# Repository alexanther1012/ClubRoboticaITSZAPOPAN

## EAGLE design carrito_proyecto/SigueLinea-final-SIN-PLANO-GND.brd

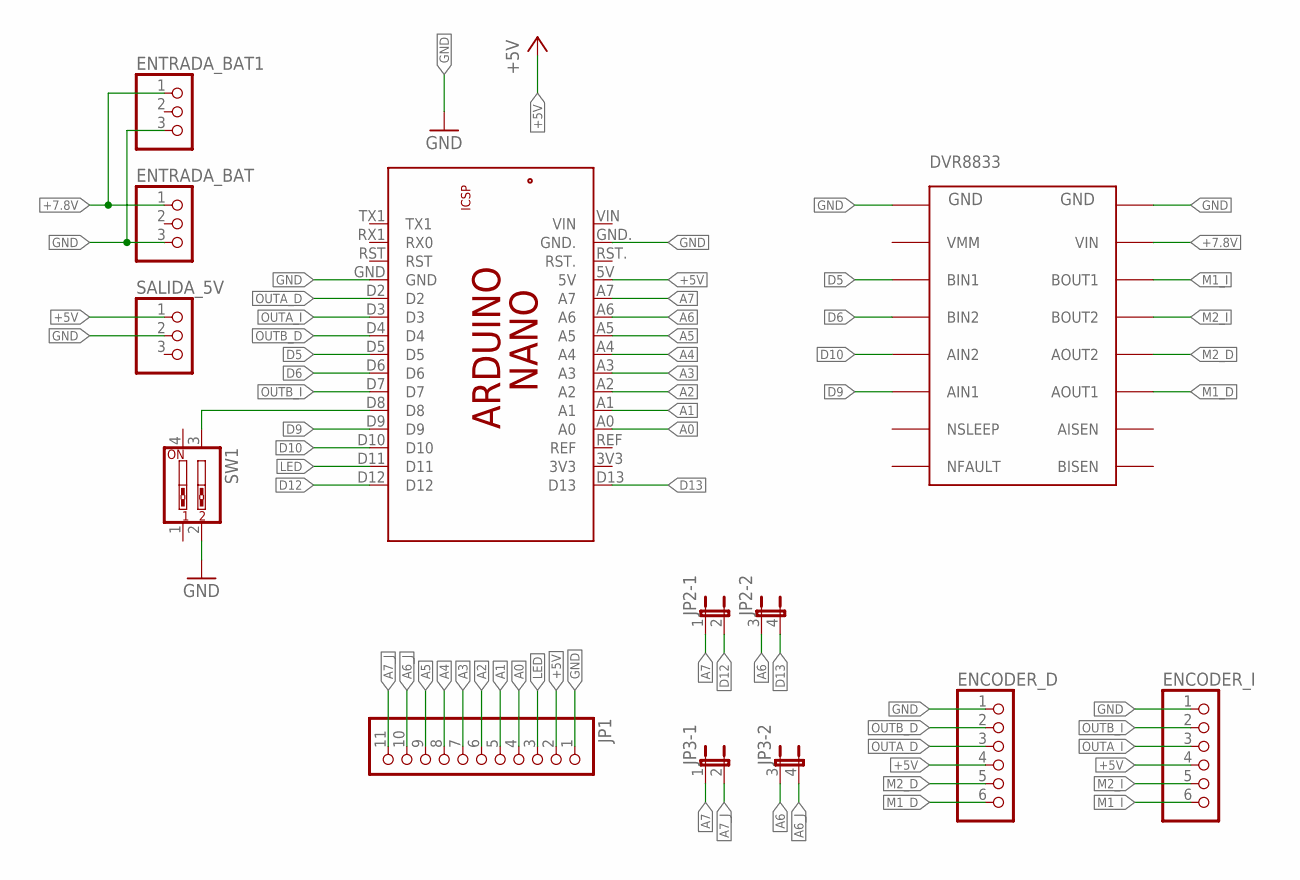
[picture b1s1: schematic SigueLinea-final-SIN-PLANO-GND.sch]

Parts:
DVR8833: DRV8833
ENCODER_D: PINHD-1X6; 1X06
ENCODER_I: PINHD-1X6; 1X06
ENTRADA_BAT, ENTRADA_BAT1: PINHD-1X3; 1X03
JP1: PINHD-1X11; 1X11
JP2, JP3: JP2QE; JP2Q
PCB1: ARDUINO_NANO
SALIDA_5V: PINHD-1X3; 1X03
SW1: SW_DIP-2; EDG-02

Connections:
+5V: ENCODER_D.4, ENCODER_I.4, JP1.2, PCB1.5V, SALIDA_5V.1
+7.8V: DVR8833.VIN, ENTRADA_BAT.1, ENTRADA_BAT1.1
A0: JP1.4, PCB1.A0
A1: JP1.5, PCB1.A1
A2: JP1.6, PCB1.A2
A3: JP1.7, PCB1.A3
A4: JP1.8, PCB1.A4
A5: JP1.9, PCB1.A5
A6: JP2.3 (1), JP3.3 (1), PCB1.A6
A6_J: JP1.10, JP3.4 (2)
A7: JP2.1, JP3.1, PCB1.A7
A7_J: JP1.11, JP3.2
D5: DVR8833.BIN1, PCB1.D5
D6: DVR8833.BIN2, PCB1.D6
D9: DVR8833.AIN1, PCB1.D9
D10: DVR8833.AIN2, PCB1.D10
D12: JP2.2, PCB1.D12
D13: JP2.4 (2), PCB1.D13
GND: DVR8833.GND1, DVR8833.GND2, ENCODER_D.1, ENCODER_I.1, ENTRADA_BAT.3, ENTRADA_BAT1.3, JP1.1, PCB1.GND, PCB1.GND., SALIDA_5V.2, SW1.2
LED: JP1.3, PCB1.D11
M1_D: DVR8833.AOUT1, ENCODER_D.6
M1_I: DVR8833.BOUT1, ENCODER_I.6
M2_D: DVR8833.AOUT2, ENCODER_D.5
M2_I: DVR8833.BOUT2, ENCODER_I.5
unnamed: PCB1.D8, SW1.3
OUTA_D: ENCODER_D.3, PCB1.D2
OUTA_I: ENCODER_I.3, PCB1.D3
OUTB_D: ENCODER_D.2, PCB1.D4
OUTB_I: ENCODER_I.2, PCB1.D7

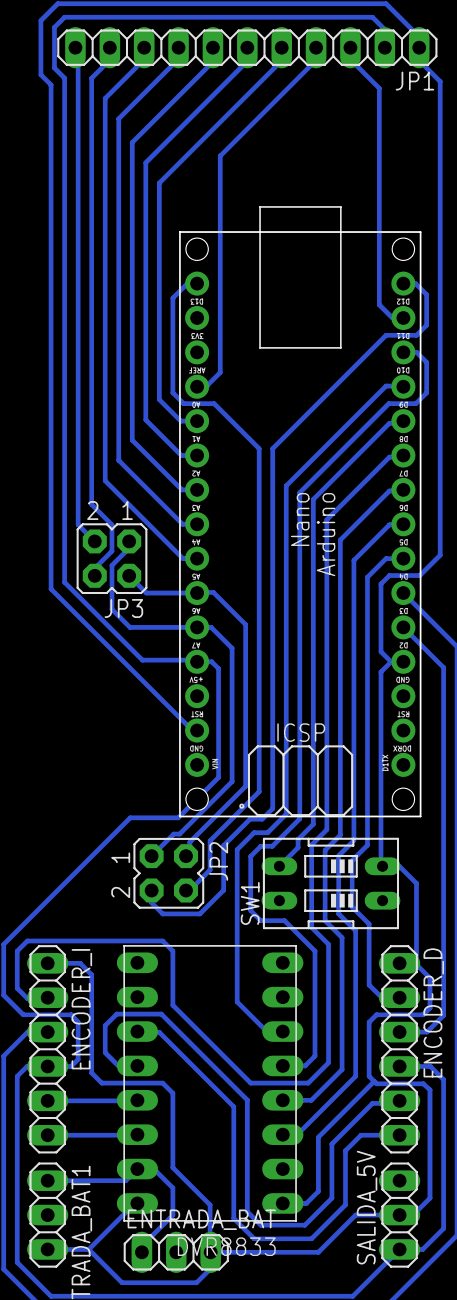
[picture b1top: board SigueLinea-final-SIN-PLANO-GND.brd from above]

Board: 2 copper layers, 11 parts (0 on the bottom side), 29 nets.

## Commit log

2015-11-27 camisa propuesta 1
    propuestas para las camisas que podríamos mandar a hacer
2015-11-27 Revert "camisa propuesta 1"
    This reverts commit 97343804daac0382864539e273942d955bd12ba9.
2015-11-27 Revert "Revert "camisa propuesta 1""
    This reverts commit 245b329fab7970d9915bdb962c6a92b57cf9aae5.
2015-11-27 reinicio
2015-11-27 camisas robotica itszapopan
    es uno de los modelos de camisa propuestas para mandar hacer
2015-11-27 camisas robotica itszapopan
    segundo modelo de camisas propuestas para el club de robotica
2015-11-27 libreria new ping sensor de proximidad
    esta libreria se usa para el sensor sonico o sensor de proximidad
2015-11-27 preactica 1 grupo de los miercoles
    blink o led parpadeante
2015-11-27 practica 2 semaforo impreso
    este semaforo se hace por medio de impresiones en el monitos serial
2015-11-27 practica 3 sensor de proximidad
    en esta practica se realizo el uso del sensor ultrasonico para medir la
    proximidad de un objeto detectado por el mismo. NOTA:Es necesaria el uso
    de la libreria NewPing
2015-11-27 Uso del bluetooth
    En esta practica se muestra el uso del bluetooth asi como el como
    utilizar appInventor para realizar la aplicacion para la comunicacion
    serial bluetooth con el arduino y un celular o dispositivo android
2015-11-27 contador 3 bits
    Este proyecto simula un contador de 3 bits con leds
2015-11-27 hola mundo
    tradicional blink o flash de led con arduino
2015-11-27 basico del puerto serial
    En este proyecto de arduino se muestra una parte basica del uso del
    puerto serial del arduino
2015-11-27 control universal basico
    En este proyecto se realizo la programacion de un control para un
    explorador simple(carrito control remoto)
2015-11-27 semaforos secuenciales
    En este proyecto se realizo la programacion de un par de semaforos
    secuenciales con arduino
2015-11-27 practica 1 grupo de los viernes
    blink o led parpadeante
2015-11-27 practica 2 grupo de los viernes semaforo simple
    Semaforo con ciclos
2015-11-28 practica 3 lectura y escritura serial
    En esta practica se realiza el uso del puerto serial para recibir datos
    e imprimirlos por medio del monitor serial
2015-11-28 cursos arduino
    apoyo para basicos de arduino
2016-04-12 material
    material extra
2016-04-12 carrito siguelineas
    esta es la ultima version vigente del carrito sigue lineas
